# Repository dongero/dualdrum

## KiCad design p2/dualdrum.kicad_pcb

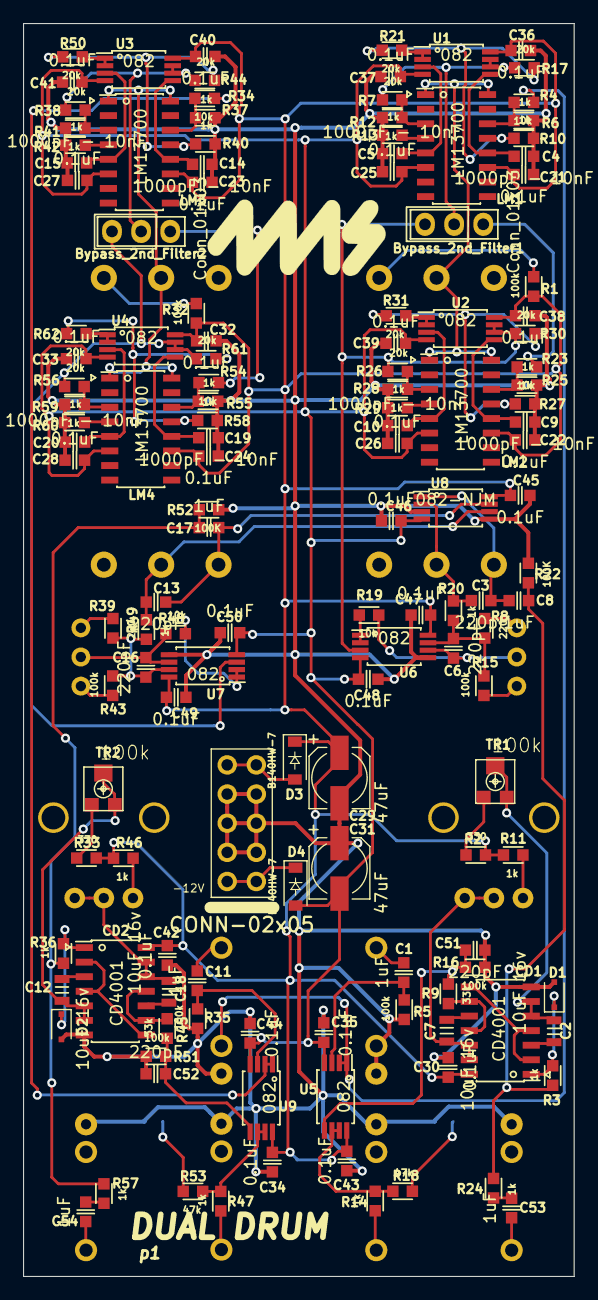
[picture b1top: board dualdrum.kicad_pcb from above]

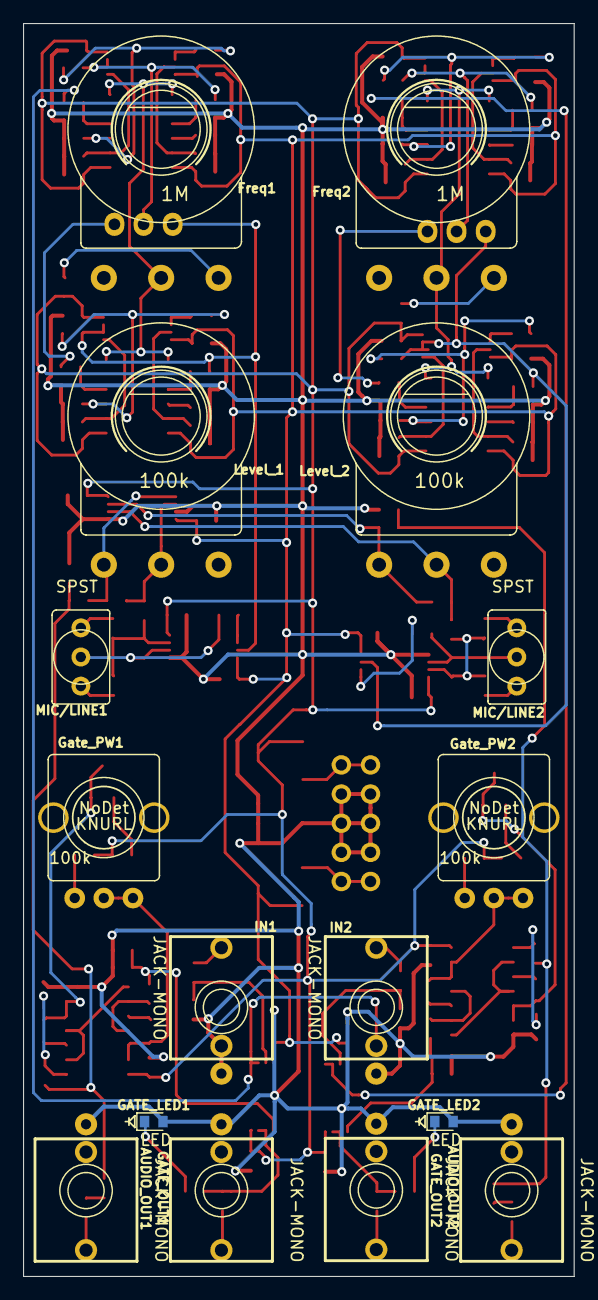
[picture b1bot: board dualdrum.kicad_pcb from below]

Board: 2 copper layers, 48.0 x 109.2 mm, 156 parts (16 on the bottom side), 95 nets.

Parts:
AUDIO_OUT1, AUDIO_OUT2: JACK-MONO; EighthInch_PJ398SM
Bypass_2nd_Filter1, Bypass_2nd_Filter2: Conn_01x03; Pins_1x03_2.54mm_TH
C1, C8, C11, C17, C53, C54: 1uF; C_0603
C2, C7, C12, C18: 10uF 16v; C_0805
C3, C6, C13, C16, C51, C52: 220pF; C_0603
C4, C5, C9, C10, C14, C15, C19, C20: 1000pF - 10nF; C_0603
C21, C22, C23, C24, C25, C26, C27, C28, C30, C32, C33, C34, C35, C36, C37, C38, C39, C40, C41, C42, C43, C44, C45, C46, C47, C48, C49, C50: 0.1uF; C_0603
C29, C31: 47uF; CP_Elec_5x5.3
CD1, CD2: CD4001; SOIC-14_3.9x8.65mm_Pitch1.27mm
D1, D2: SD103; D_SOD-323F
D3, D4: B140HW-7; D_SOD-123
Freq1, Freq2: 1M; Pot_16mm_NoDet_RV16AF-4A
GATE_LED1, GATE_LED2: LED; LED_0603_1608Metric
GATE_OUT1, GATE_OUT2: JACK-MONO; EighthInch_PJ398SM
Gate_PW1, Gate_PW2: 100k; Pot_9mm_Knurl_NoDet
IN1, IN2: JACK-MONO; EighthInch_PJ398SM
LM1, LM2, LM3, LM4: LM13700; SOIC-16_3.9x9.9mm_Pitch1.27mm
Level_1, Level_2: 100k; Pot_16mm_NoDet_RV16AF-4A
MIC/LINE1, MIC/LINE2: SPST; Switch_Toggle_SPDT_SubMini
P1: CONN-02x05; Pins_2x05_2.54mm_TH_Europower
R1, R5, R15, R16, R32, R35, R43, R51: 100k; R_0603
R2, R33: 330; R_0603
R3, R6, R10, R11, R12, R13, R14, R20, R24, R25, R27, R28, R29, R36, R37, R40, R41, R42, R46, R47, R49, R55, R57, R58, R59, R60: 1k; R_0603
R4, R19, R23, R34, R48, R54: 10k; R_0603
R7, R17, R21, R26, R30, R31, R38, R44, R50, R56, R61, R62: 20k; R_0603
R8, R39: 220; R_0603
R9, R45: 33k; R_0603
R18, R53: 47k; R_0603
R22, R52: 100K; R_0603
TR1, TR2: 100k; Pot_Trim_SMT_TC33X
U1, U2, U3, U4, U5, U6, U7, U9: 082; TSSOP-8_4.4x3mm_Pitch0.65mm
U8: 082-NJM; TSSOP-8_4.4x3mm_Pitch0.65mm

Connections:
+12V: C21.1, C22.1, C23.1, C24.1, C29.1, C30.1, C32.1, C34.1, C36.1, C38.1, C40.1, C42.1, C43.1, C45.1, C47.1, C49.1, CD1.14, CD2.14, D3.1, LM1.11, LM2.11, LM3.11, LM4.11, R1.1, R2.2, R11.2, R32.1, R33.2, R46.2, U1.8, U2.8, U3.8, U4.8, U5.8, U6.8, U7.8, U8.8, U9.8
-12VA: C25.1, C26.1, C27.1, C28.1, C31.2, C33.1, C35.1, C37.1, C39.1, C41.1, C44.1, C46.1, C48.1, C50.1, D4.2, LM1.6, LM2.6, LM3.6, LM4.6, U1.4, U2.4, U3.4, U4.4, U5.4, U6.4, U7.4, U8.4, U9.4
GND: AUDIO_OUT1.2, AUDIO_OUT2.2, C4.2, C5.2, C9.2, C10.2, C14.2, C15.2, C19.2, C20.2, C21.2, C22.2, C23.2, C24.2, C25.2, C26.2, C27.2, C28.2, C29.2, C30.2, C31.1, C32.2, C33.2, C34.2, C35.2, C36.2, C37.2, C38.2, C39.2, C40.2, C41.2, C42.2, C43.2, C44.2, C45.2, C46.2, C47.2, C48.2, C49.2, C50.2, C51.2, C52.2, CD1.7, CD2.7, D1.2, D2.2, GATE_LED1.2, GATE_LED2.2, GATE_OUT1.2, GATE_OUT2.2, IN1.2, IN1.3, IN2.2, P1.3, P1.4, P1.5, P1.6, P1.7, P1.8, R5.1, R6.2, R10.2, R12.2, R13.1, R16.1, R22.1, R25.2, R27.2, R28.2, R29.1, R35.1, R37.2, R40.2, R41.2, R42.1, R51.1, R52.1, R55.2, R58.2, R59.2, R60.1, U6.5, U7.5, U8.3, U8.5
unnamed: AUDIO_OUT1.1, C53.2
unnamed: AUDIO_OUT2.1, C54.2
unnamed: Bypass_2nd_Filter1.1, R26.1, R30.1, U2.6, U2.7, U6.3
unnamed: Bypass_2nd_Filter1.2, R7.1, R17.1, U1.6, U1.7
unnamed: Bypass_2nd_Filter1.3, R23.1
unnamed: Bypass_2nd_Filter2.1, R56.1, R61.1, U4.6, U4.7, U7.3
unnamed: Bypass_2nd_Filter2.2, R38.1, R44.1, U3.6, U3.7
unnamed: Bypass_2nd_Filter2.3, R54.1
unnamed: C1.1, IN1.1
unnamed: C1.2, R5.2, U5.3
unnamed: C2.1, CD1.3
unnamed: C2.2, CD1.5, CD1.6, TR1.2, TR1.3
unnamed: C3.1, Level_1.2, R20.1, U8.2
unnamed: C3.2, C8.1, Level_1.1, U8.1
unnamed: C4.1, LM1.12, U1.5
unnamed: C5.1, LM1.5, U1.3
unnamed: C6.1, MIC/LINE1.2, R19.1, U6.6
unnamed: C6.2, R8.2, R15.2, R20.2, U6.7
unnamed: C7.1, CD1.10
unnamed: C7.2, CD1.12, CD1.13, Gate_PW1.2, Gate_PW1.3
unnamed: C8.2, R3.1, R22.2, R24.1
unnamed: C9.1, LM2.12, U2.5
unnamed: C10.1, LM2.5, U2.3
unnamed: C11.1, IN2.1
unnamed: C11.2, R35.2, U9.3
unnamed: C12.1, CD2.3
unnamed: C12.2, CD2.5, CD2.6, TR2.2, TR2.3
unnamed: C13.1, Level_2.2, R49.1, U8.6
unnamed: C13.2, C17.1, Level_2.1, U8.7
unnamed: C14.1, LM3.12, U3.5
unnamed: C15.1, LM3.5, U3.3
unnamed: C16.1, MIC/LINE2.2, R48.1, U7.6
unnamed: C16.2, R39.2, R43.2, R49.2, U7.7
unnamed: C17.2, R36.1, R52.2, R57.1
unnamed: C18.1, CD2.10
unnamed: C18.2, CD2.12, CD2.13, Gate_PW2.2, Gate_PW2.3
unnamed: C19.1, LM4.12, U4.5
unnamed: C20.1, LM4.5, U4.3
unnamed: C51.1, R9.1, R16.2, U5.5
unnamed: C52.1, R45.1, R51.2, U9.5
unnamed: C53.1, R24.2
unnamed: C54.1, R57.2
unnamed: CD1.1, D1.1, R3.2
unnamed: CD1.2, CD1.4, CD1.8
unnamed: CD1.9, CD1.11, R9.2
unnamed: CD2.1, D2.1, R36.2
unnamed: CD2.2, CD2.4, CD2.8
unnamed: CD2.9, CD2.11, R45.2
unnamed: D3.2, P1.1, P1.2
unnamed: D4.1, P1.9, P1.10
unnamed: Freq1.2, LM1.1, LM1.16, LM2.1, LM2.16
unnamed: Freq1.3, R1.2
unnamed: Freq2.2, LM3.1, LM3.16, LM4.1, LM4.16
unnamed: Freq2.3, R32.2
unnamed: GATE_LED1.1, R18.2
unnamed: GATE_LED2.1, R53.2
unnamed: GATE_OUT1.1, R14.1
unnamed: GATE_OUT2.1, R47.1
unnamed: Gate_PW1.1, R11.1
unnamed: Gate_PW2.1, R46.1
unnamed: IN2.3, R4.1, U5.1, U5.2
unnamed: LM1.3, R7.2, R12.1
unnamed: LM1.4, R13.2
unnamed: LM1.13, R10.1, R17.2, R21.2
unnamed: LM1.14, R4.2, R6.1
unnamed: LM2.3, R26.2, R28.1
unnamed: LM2.4, R29.2
unnamed: LM2.13, R27.1, R30.2, R31.2
unnamed: LM2.14, R23.2, R25.1
unnamed: LM3.3, R38.2, R41.1
unnamed: LM3.4, R42.2
unnamed: LM3.13, R40.1, R44.2, R50.2
unnamed: LM3.14, R34.2, R37.1
unnamed: LM4.3, R56.2, R59.1
unnamed: LM4.4, R60.2
unnamed: LM4.13, R58.1, R61.2, R62.2
unnamed: LM4.14, R54.2, R55.1
unnamed: MIC/LINE1.1, R15.1
unnamed: MIC/LINE1.3, R8.1
unnamed: MIC/LINE2.1, R43.1
unnamed: MIC/LINE2.3, R39.1
unnamed: R2.1, TR1.1
unnamed: R14.2, R18.1, U5.6, U5.7
unnamed: R19.2, U6.1, U6.2
unnamed: R21.1, U1.1, U1.2
unnamed: R31.1, U2.1, U2.2
unnamed: R33.1, TR2.1
unnamed: R34.1, U9.1, U9.2
unnamed: R47.2, R53.1, U9.6, U9.7
unnamed: R48.2, U7.1, U7.2
unnamed: R50.1, U3.1, U3.2
unnamed: R62.1, U4.1, U4.2

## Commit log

2019-08-07 created project
2019-08-07 found 13700
2019-08-11 added notes
2019-08-14 laid 7660 circuit
2019-08-14 wip on lm13700 circuits
2019-08-14 wip incorperated PI circuit
2019-08-14 ok time to take a break
2019-08-21 added new schem + notes
2019-08-25 created dualdrumdev
2019-08-25 setup power
2019-08-26 about to annotate parts
2019-08-26 layed pots and jacks
2019-08-26 grouped components
2019-08-26 cruisin
2019-08-26 good stopping point
2019-08-27 placed all components
2019-08-27 created fp file - ready to layout dev board
2019-08-27 beginning to lay tracks
2019-08-28 finished pwr and gnd tracks
2019-08-28 about to run drc
2019-08-28 drc cleared - checking for more mistakes
2019-08-28 organized front refs
2019-08-28 organized refs - review with fresh eyes
2019-08-29 made font bigger
2019-08-29 looks good - ready to plot
2019-08-29 plotted fp gerbers
2019-08-29 generated grbs - submitted to pcbcart
2019-08-30 created pi - ready to import to 4ms git
2019-08-30 started new vco-vca-env project
2019-08-30 generated gerbers and ordered p1
2019-09-09 generated pnp machine
2019-09-25 created p2 - made notes on schematic - getting p1 to function
2019-09-26 added notes - made more tests
2020-02-21 p2 notes
